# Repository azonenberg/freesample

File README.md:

# freesample
High performance sampling oscilloscope based on INTEGRALSTICK

Separate board talking to AC701 since we need a GTP
	Use a XM105 if we need more GPIO and

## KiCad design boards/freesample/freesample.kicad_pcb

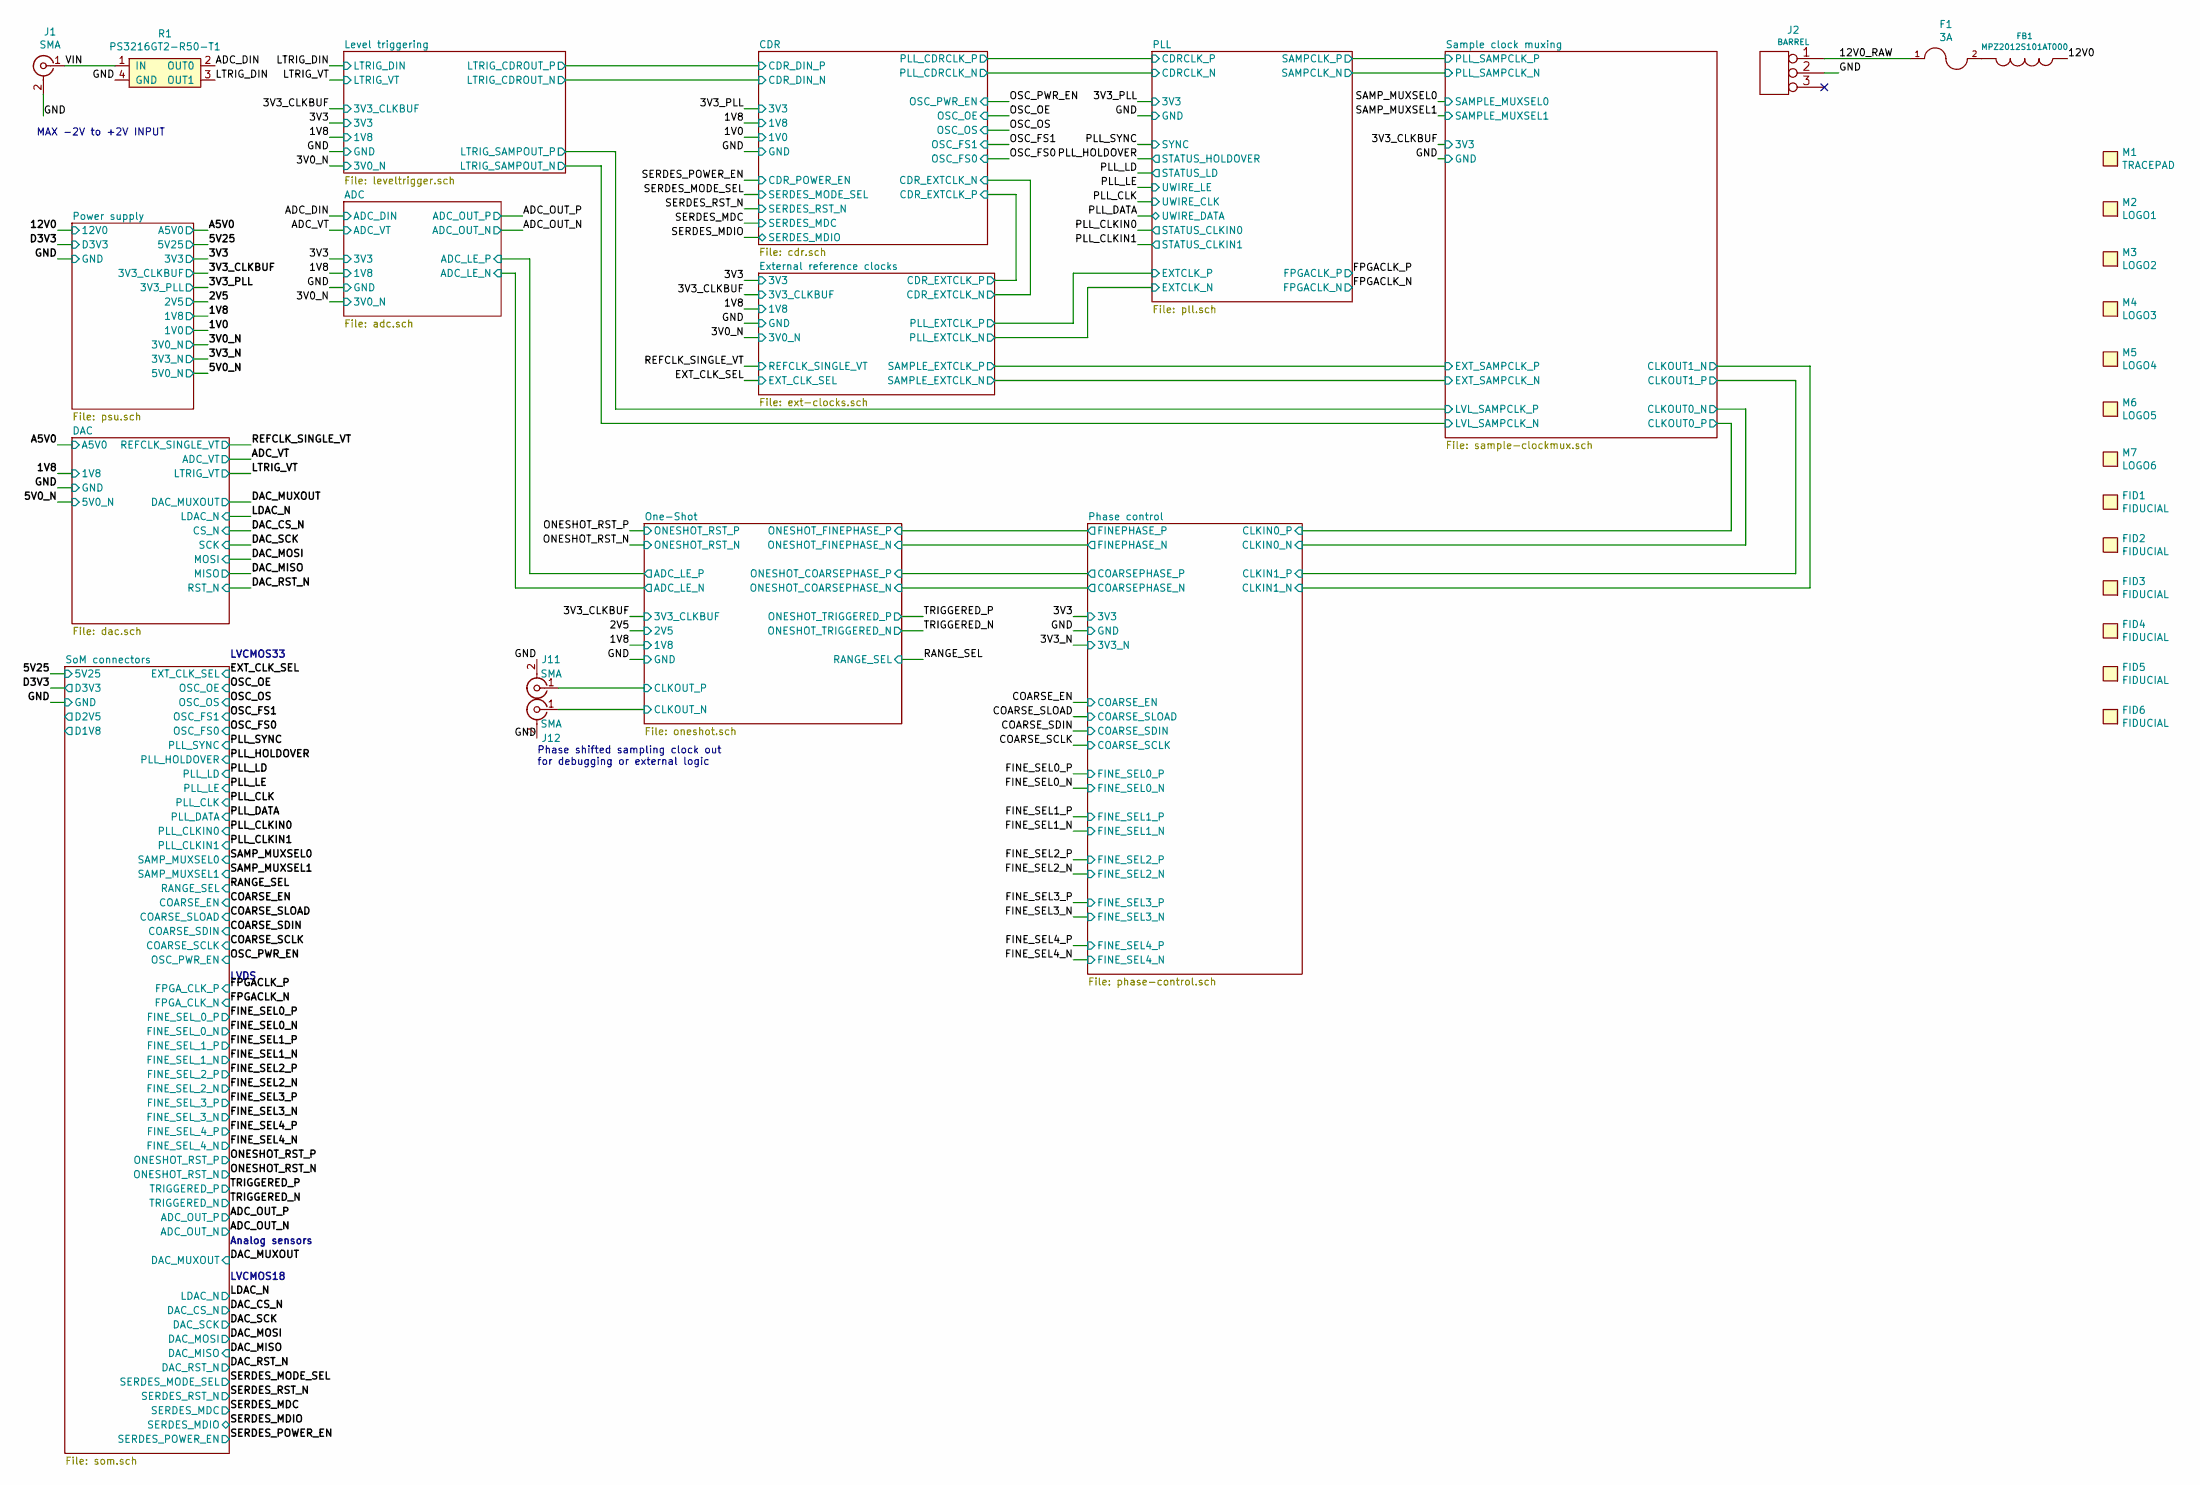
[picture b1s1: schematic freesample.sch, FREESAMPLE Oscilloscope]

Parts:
F1: 3A; EIA_0603_RES_NOSILK
FB1: MPZ2012S101AT000; EIA_0805_CAP_NOSILK
FID1, FID2, FID3, FID4, FID5, FID6: FIDUCIAL; FIDUCIAL_1MM
J1, J11, J12: SMA; CONN_SMA_EDGE_SAMTEC_SMA_J_P_H_ST_EM1
J2: BARREL; CONN_CUI_PJ-058BH_HIPWR_BARREL_NOSLOT
M1: TRACEPAD; SERIALNUM_MOLEX_0916580020
M2: LOGO1; LONGTHING-1200DPI
M3: LOGO2; Logo_silk_OSHW_6x6mm
M4: LOGO3; Logo_silk_polarity_center_5x1.4mm
M5: LOGO4; Logo_silk_ROHS_5x2.8mm
M6: LOGO5; Logo_silk_warning_5x4.2mm
M7: LOGO6; Logo_silk_WEEE_3.4x5mm
R1: PS3216GT2-R50-T1‎; SPLITTER_SUSUMU_PS3216G

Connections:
/12V0: FB1.1; also elsewhere on the board
/12V0_RAW: F1.1, J2.1
/ADC_DIN: R1.2 (OUT0); also elsewhere on the board
/GND: J1.2 (Ext), J2.2 (PM), J11.2 (Ext), J12.2 (Ext), R1.4 (GND); also elsewhere on the board
/LTRIG_DIN: R1.3 (OUT1); also elsewhere on the board
/One-Shot/CLKOUT_N: J12.1 (In); also elsewhere on the board
/One-Shot/CLKOUT_P: J11.1 (In); also elsewhere on the board
/VIN: J1.1 (In), R1.1 (IN)
unnamed: F1.2, FB1.2

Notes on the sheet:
LVCMOS33
Analog sensors
LVCMOS18
MAX -2V to +2V INPUT
LVDS
Phase shifted sampling clock out for debugging or external logic

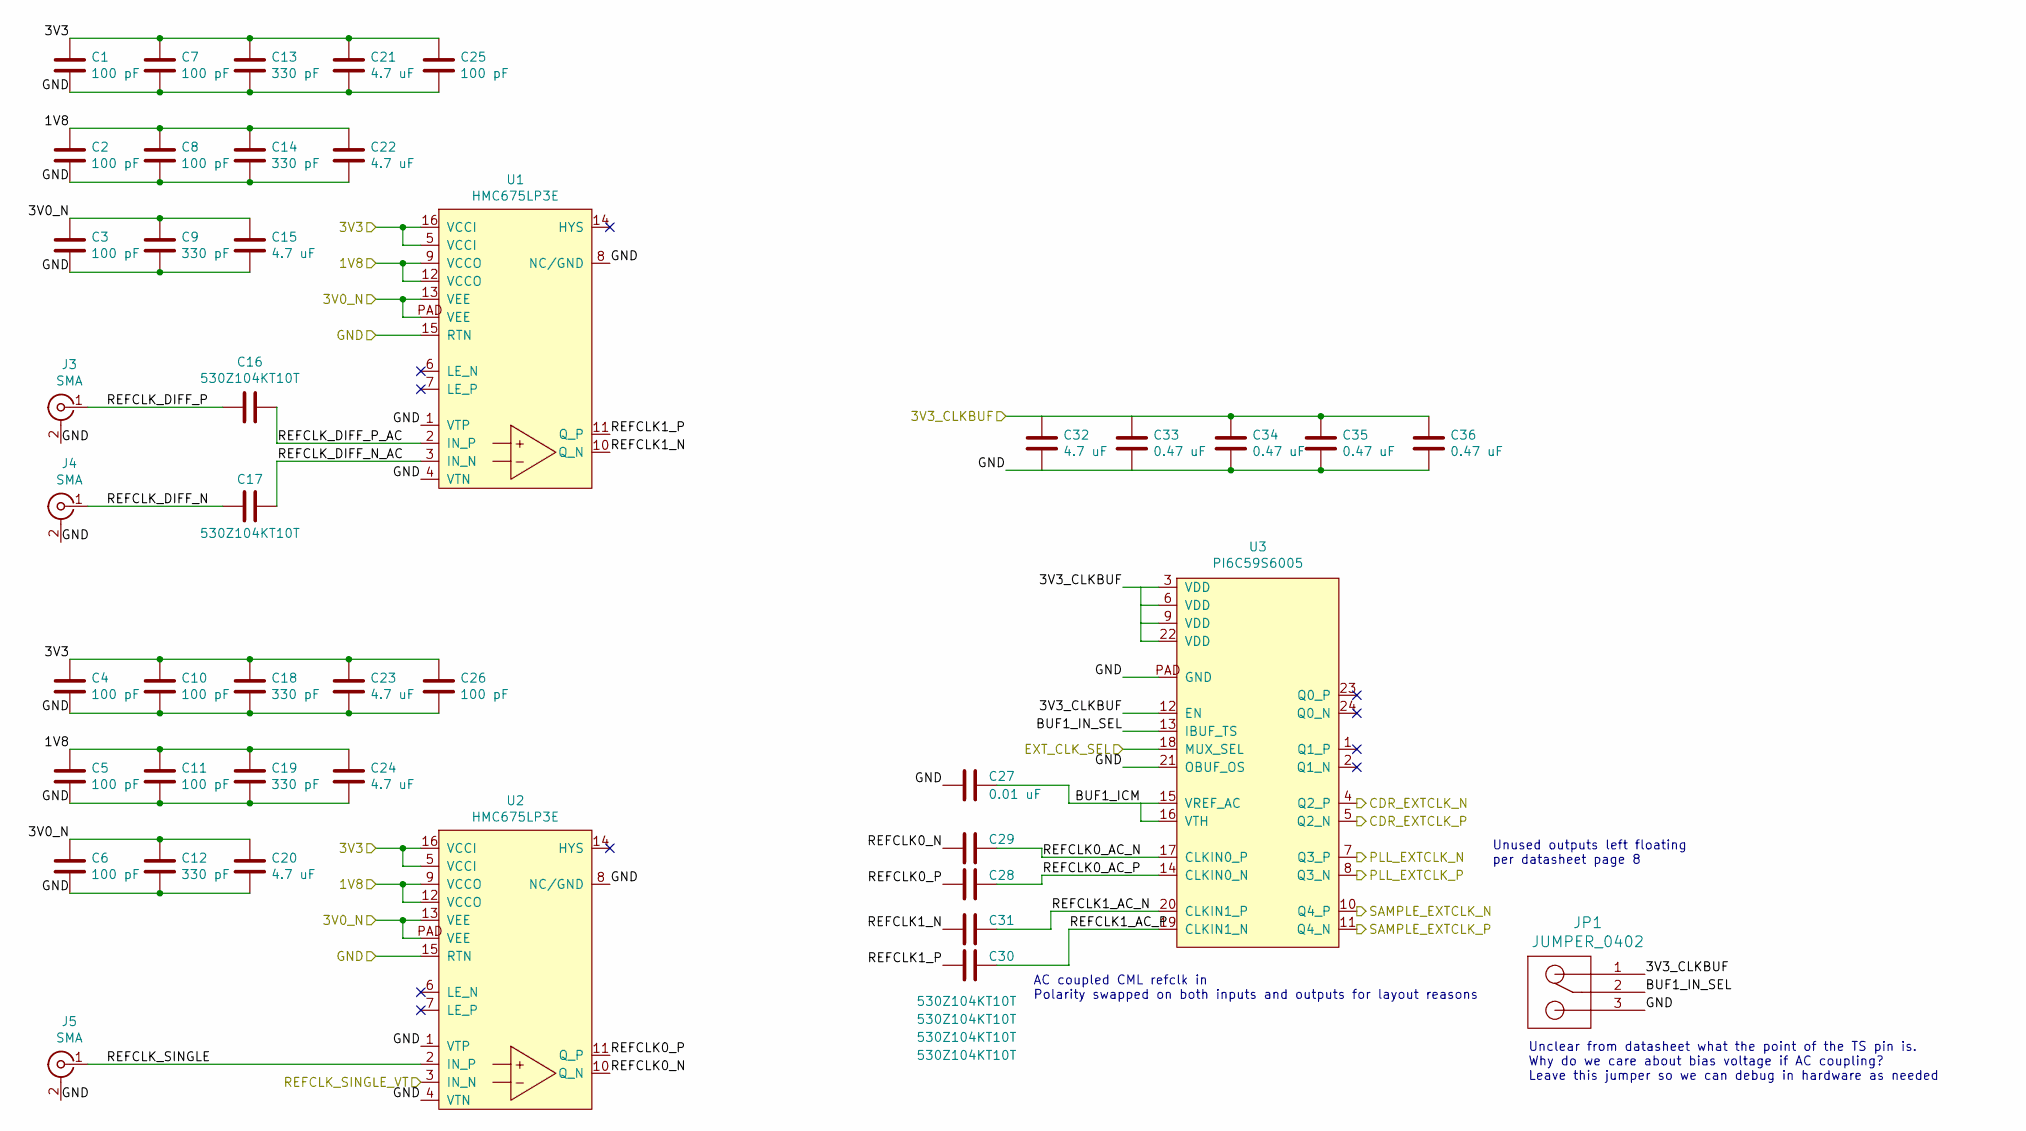
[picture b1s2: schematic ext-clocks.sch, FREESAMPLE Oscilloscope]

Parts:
C1, C2, C3, C4, C5, C6, C7, C8, C10, C11, C25, C26: 100 pF; EIA_0201_CAP_NOSILK
C9, C12, C13, C14, C18, C19: 330 pF; EIA_0201_CAP_NOSILK
C15, C20, C21, C22, C23, C24, C32: 4.7 uF; EIA_0603_CAP_NOSILK
C16, C17, C28, C29, C30, C31: 530Z104KT10T; EIA_0201_CAP_NOSILK
C27: 0.01 uF; EIA_0402_CAP_NOSILK
C33, C34, C35, C36: 0.47 uF; EIA_0402_CAP_NOSILK
J3, J4, J5: SMA; CONN_SMA_EDGE_SAMTEC_SMA_J_P_H_ST_EM1
JP1: JUMPER_0402; EIA_0402_JUMPER
U1, U2: HMC675LP3E; QFN_16_0.5MM_3x3MM
U3: PI6C59S6005; QFN_24_0.5MM_4x4MM

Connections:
/1V8: C2.1, C5.1, C8.1, C11.1, C14.1, C19.1, C22.1, C24.1, U1.9 (VCCO), U1.12 (VCCO), U2.9 (VCCO), U2.12 (VCCO); also elsewhere on the board
/3V0_N: C3.1, C6.1, C9.1, C12.1, C15.1, C20.1, U1.13 (VEE), U1.PAD (VEE), U2.13 (VEE), U2.PAD (VEE); also elsewhere on the board
/3V3: C1.1, C4.1, C7.1, C10.1, C13.1, C18.1, C21.1, C23.1, C25.1, C26.1, U1.5 (VCCI), U1.16 (VCCI), U2.5 (VCCI), U2.16 (VCCI); also elsewhere on the board
/3V3_CLKBUF: C32.1, C33.1, C34.1, C35.1, C36.1, JP1.1, U3.3 (VDD), U3.6 (VDD), U3.9 (VDD), U3.12 (EN), U3.22 (VDD); also elsewhere on the board
/CDR/CDR_EXTCLK_N: U3.4 (Q2_P); also elsewhere on the board
/CDR/CDR_EXTCLK_P: U3.5 (Q2_N); also elsewhere on the board
/EXT_CLK_SEL: U3.18 (MUX_SEL); also elsewhere on the board
/External reference clocks/BUF1_ICM: C27.1, U3.15 (VREF_AC), U3.16 (VTH)
/External reference clocks/BUF1_IN_SEL: JP1.2, U3.13 (IBUF_TS)
/External reference clocks/REFCLK0_AC_N: C29.1, U3.17 (CLKIN0_P)
/External reference clocks/REFCLK0_AC_P: C28.1, U3.14 (CLKIN0_N)
/External reference clocks/REFCLK0_N: C29.2, U2.10 (Q_N)
/External reference clocks/REFCLK0_P: C28.2, U2.11 (Q_P)
/External reference clocks/REFCLK1_AC_N: C31.1, U3.20 (CLKIN1_P)
/External reference clocks/REFCLK1_AC_P: C30.1, U3.19 (CLKIN1_N)
/External reference clocks/REFCLK1_N: C31.2, U1.10 (Q_N)
/External reference clocks/REFCLK1_P: C30.2, U1.11 (Q_P)
/External reference clocks/REFCLK_DIFF_N: C17.2, J4.1 (In)
/External reference clocks/REFCLK_DIFF_N_AC: C17.1, U1.3 (IN_N)
/External reference clocks/REFCLK_DIFF_P: C16.2, J3.1 (In)
/External reference clocks/REFCLK_DIFF_P_AC: C16.1, U1.2 (IN_P)
/External reference clocks/REFCLK_SINGLE: J5.1 (In), U2.2 (IN_P)
/GND: C1.2, C2.2, C3.2, C4.2, C5.2, C6.2, C7.2, C8.2, C9.2, C10.2, C11.2, C12.2, C13.2, C14.2, C15.2, C18.2, C19.2, C20.2, C21.2, C22.2, C23.2, C24.2, C25.2, C26.2, C27.2, C32.2, C33.2, C34.2, C35.2, C36.2, J3.2 (Ext), J4.2 (Ext), J5.2 (Ext), JP1.3, U1.1 (VTP), U1.4 (VTN), U1.8 (NC/GND), U1.15 (RTN), U2.1 (VTP), U2.4 (VTN), U2.8 (NC/GND), U2.15 (RTN), U3.21 (OBUF_OS), U3.PAD (GND); also elsewhere on the board
/PLL/EXTCLK_N: U3.7 (Q3_P); also elsewhere on the board
/PLL/EXTCLK_P: U3.8 (Q3_N); also elsewhere on the board
/REFCLK_SINGLE_VT: U2.3 (IN_N); also elsewhere on the board
/Sample clock muxing/EXT_SAMPCLK_N: U3.10 (Q4_P); also elsewhere on the board
/Sample clock muxing/EXT_SAMPCLK_P: U3.11 (Q4_N); also elsewhere on the board

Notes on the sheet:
AC coupled CML refclk in Polarity swapped on both inputs and outputs for layout reasons
Unused outputs left floating per datasheet page 8
Unclear from datasheet what the point of the TS pin is. Why do we care about bias voltage if AC coupling? Leave this jumper so we can debug in hardware as needed

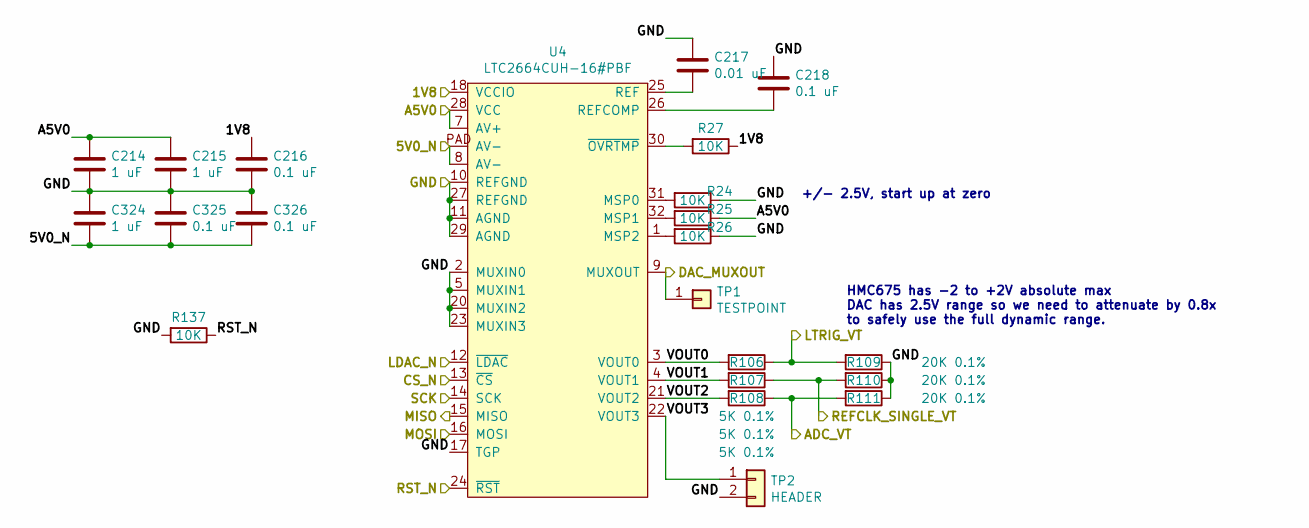
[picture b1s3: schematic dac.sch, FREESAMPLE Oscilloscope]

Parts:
C214, C215, C324: 1 uF; EIA_0603_CAP_NOSILK
C216, C218, C325, C326: 0.1 uF; EIA_0402_CAP_NOSILK
C217: 0.01 uF; EIA_0402_CAP_NOSILK
R24, R25, R26, R27, R137: 10K; EIA_0402_RES_NOSILK
R106, R107, R108: 5K 0.1%; EIA_0402_RES_NOSILK
R109, R110, R111: 20K 0.1%; EIA_0402_RES_NOSILK
TP1: TESTPOINT; TESTPOINT_SMT_KEYSTONE_5016
TP2: HEADER; CONN_HEADER_2.54MM_1x2
U4: LTC2664CUH-16#PBF; QFN_32_0.5MM_5x5MM

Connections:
/1V8: C216.1, R27.1, U4.18 (VCCIO); also elsewhere on the board
/5V0_N: C324.2, C325.2, C326.2, U4.8 (AV-), U4.PAD (AV-); also elsewhere on the board
/A5V0: C214.1, C215.1, R25.1, U4.7 (AV+), U4.28 (VCC); also elsewhere on the board
/ADC_VT: R108.1, R111.2; also elsewhere on the board
/DAC/VOUT0: R106.2, U4.3 (VOUT0)
/DAC/VOUT1: R107.2, U4.4 (VOUT1)
/DAC/VOUT2: R108.2, U4.21 (VOUT2)
/DAC/VOUT3: TP2.1, U4.22 (VOUT3)
/DAC_CS_N: U4.13 (~CS); also elsewhere on the board
/DAC_MISO: U4.15 (MISO); also elsewhere on the board
/DAC_MOSI: U4.16 (MOSI); also elsewhere on the board
/DAC_MUXOUT: TP1.1, U4.9 (MUXOUT); also elsewhere on the board
/DAC_RST_N: R137.1, U4.24 (~RST); also elsewhere on the board
/DAC_SCK: U4.14 (SCK); also elsewhere on the board
/GND: C214.2, C215.2, C216.2, C217.1, C218.1, C324.1, C325.1, C326.1, R24.1, R26.1, R109.1, R110.1, R111.1, R137.2, TP2.2, U4.2 (MUXIN0), U4.5 (MUXIN1), U4.10 (REFGND), U4.11 (AGND), U4.17 (TGP), U4.20 (MUXIN2), U4.23 (MUXIN3), U4.27 (REFGND), U4.29 (AGND); also elsewhere on the board
/LDAC_N: U4.12 (~LDAC); also elsewhere on the board
/LTRIG_VT: R106.1, R109.2; also elsewhere on the board
/REFCLK_SINGLE_VT: R107.1, R110.2; also elsewhere on the board
unnamed: C217.2, U4.25 (REF)
unnamed: C218.2, U4.26 (REFCOMP)
unnamed: R24.2, U4.31 (MSP0)
unnamed: R25.2, U4.32 (MSP1)
unnamed: R26.2, U4.1 (MSP2)
unnamed: R27.2, U4.30 (~OVRTMP)

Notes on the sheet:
+/- 2.5V, start up at zero
HMC675 has -2 to +2V absolute max DAC has 2.5V range so we need to attenuate by 0.8x to safely use the full dynamic range.

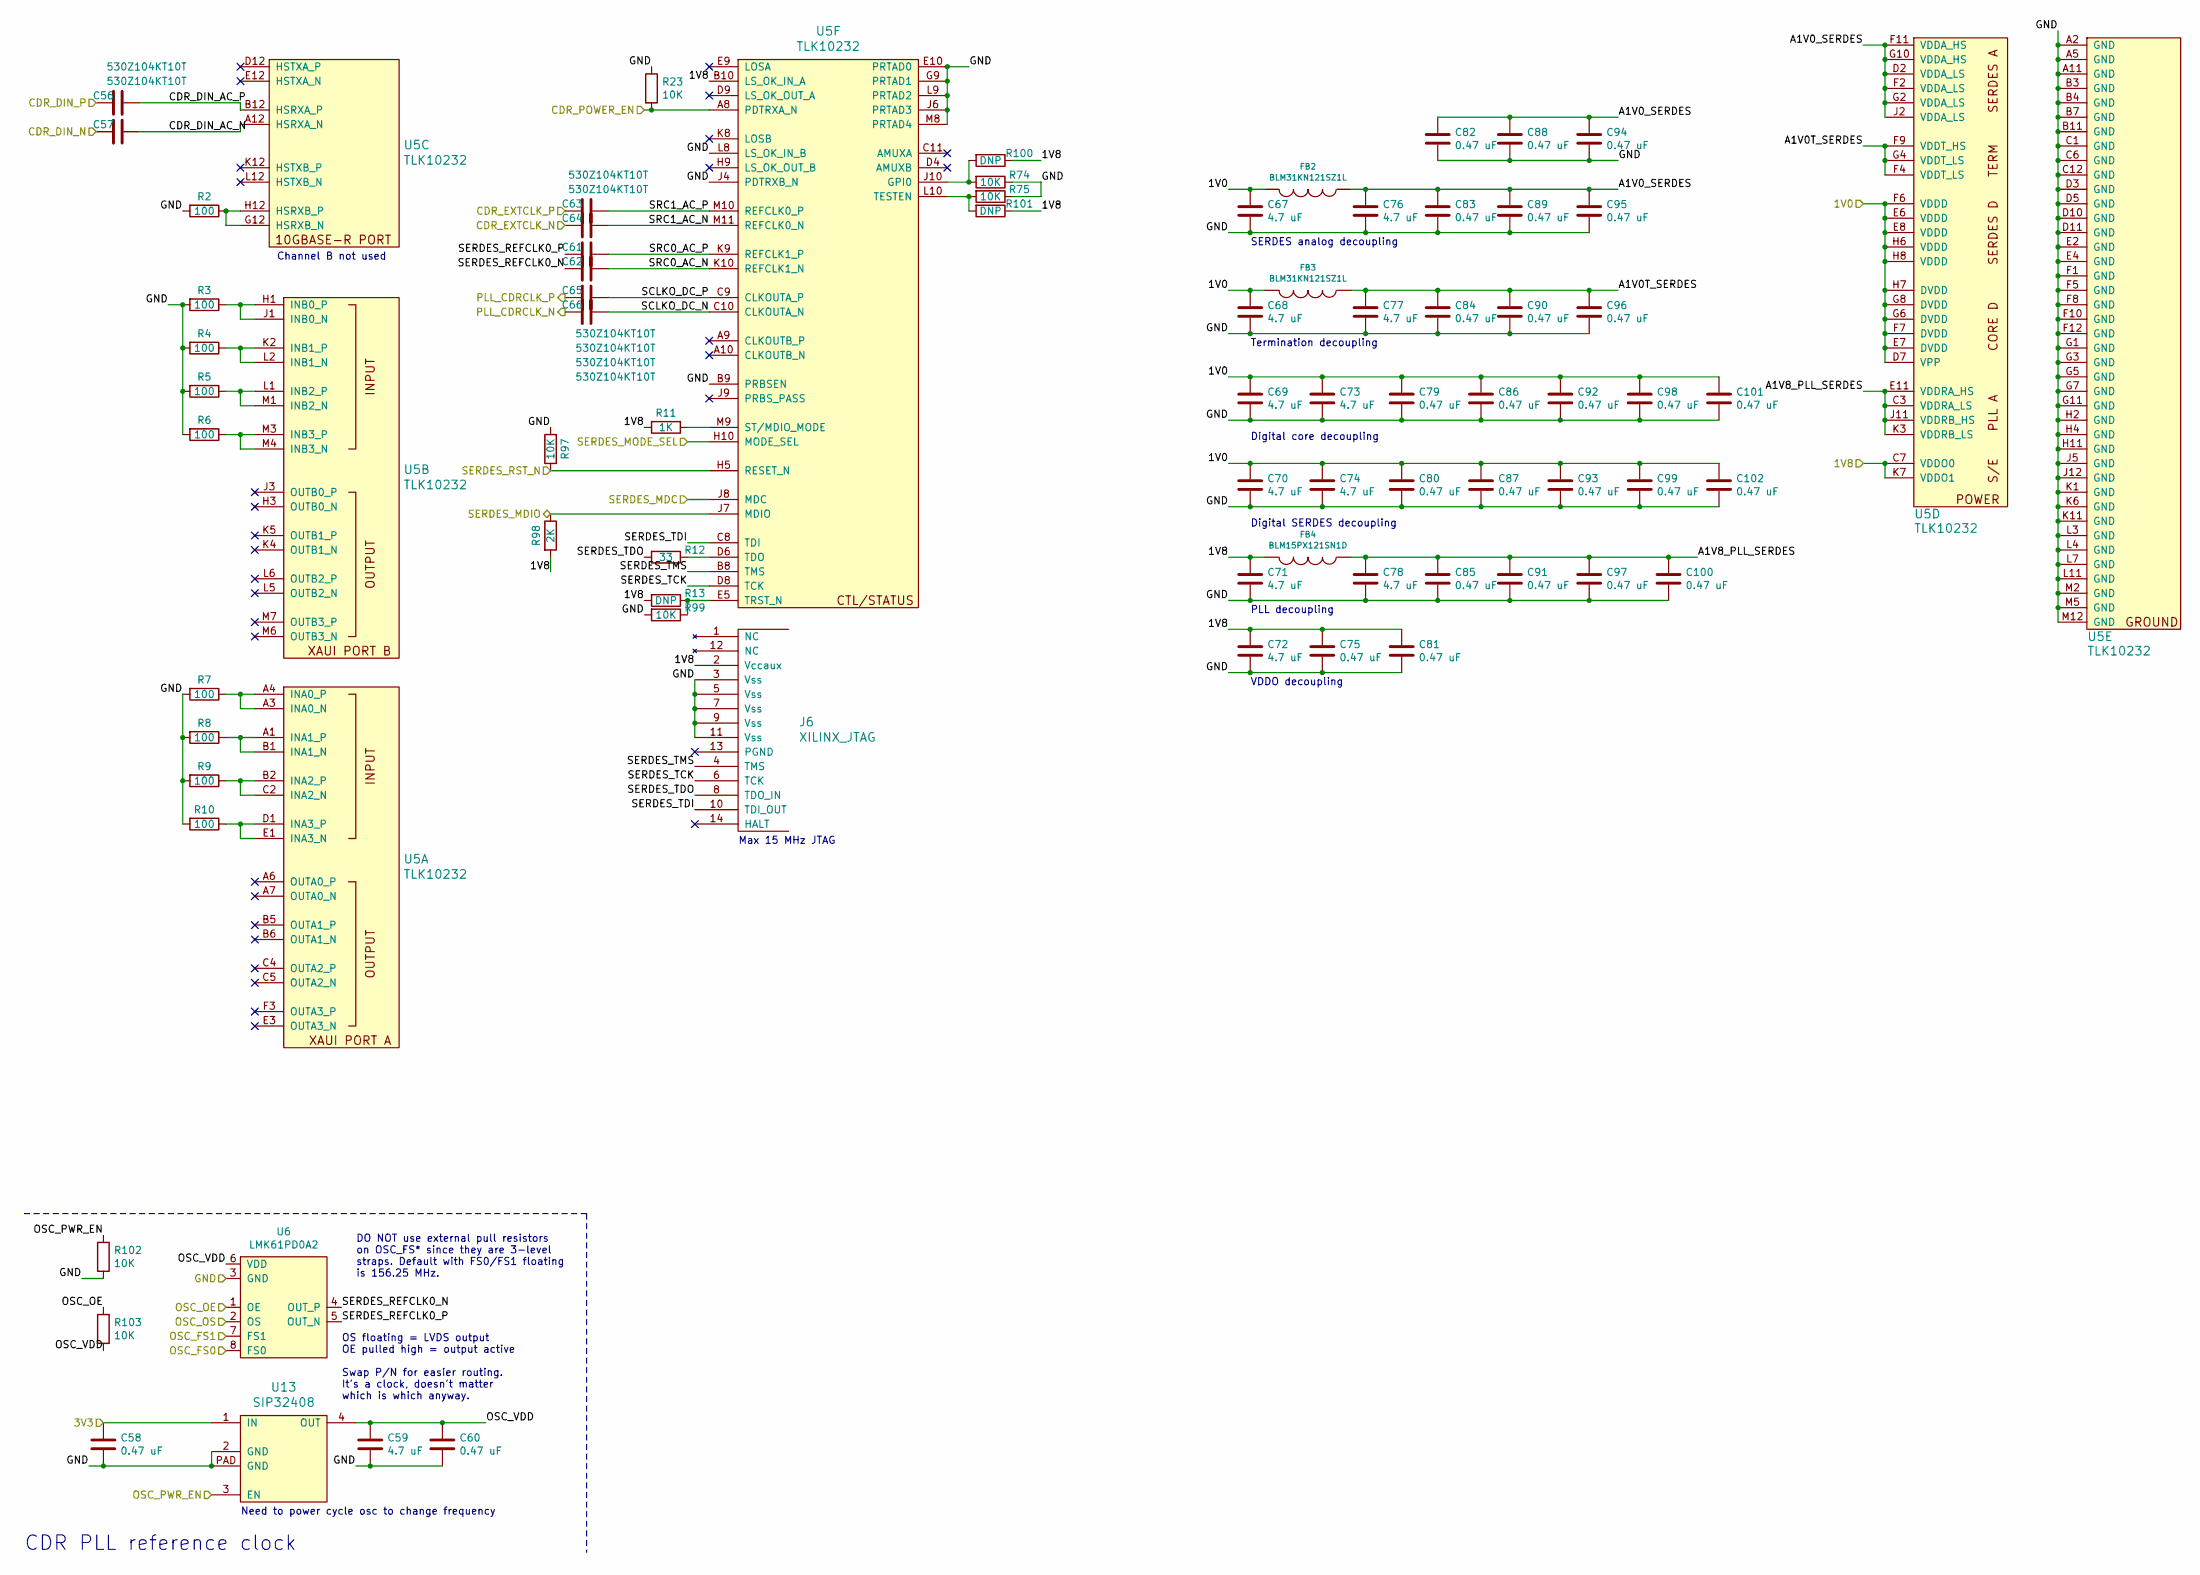
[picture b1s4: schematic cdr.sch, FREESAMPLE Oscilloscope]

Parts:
C56, C57, C61, C62, C63, C64, C65, C66: 530Z104KT10T; EIA_0201_CAP_NOSILK
C58, C60, C75, C79, C80, C81, C82, C83, C84, C85, C86, C87, C88, C89, C90, C91, C92, C93, C94, C95, C96, C97, C98, C99, C100, C101, C102: 0.47 uF; EIA_0402_CAP_NOSILK
C59, C67, C68, C69, C70, C71, C72, C73, C74, C76, C77, C78: 4.7 uF; EIA_0603_CAP_NOSILK
FB2, FB3: BLM31KN121SZ1L; EIA_1206_CAP_NOSILK
FB4: BLM15PX121SN1D; EIA_0402_CAP_NOSILK
J6: XILINX_JTAG; XILINX_JTAG_PTH_MOLEX_0878311420
R2, R3, R4, R5, R6, R7, R8, R9, R10: 100; EIA_0402_RES_NOSILK
R11: 1K; EIA_0402_RES_NOSILK
R12: 33; EIA_0402_RES_NOSILK
R13, R100, R101: DNP; EIA_0402_RES_NOSILK
R23, R74, R75, R97, R99, R102, R103: 10K; EIA_0402_RES_NOSILK
R98: 2K; EIA_0402_RES_NOSILK
U5: TLK10232; BGA_144_13x13_FULLARRAY_1MM
U6: LMK61PD0A2; QFN_8_5x7MM_TI_SIA
U13: SIP32408; DFN_4_0.5MM_1.6x1.2MM

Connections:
/1V0: C67.1, C68.1, C69.1, C70.1, C73.1, C74.1, C79.1, C80.1, C86.1, C87.1, C92.1, C93.1, C98.1, C99.1, C101.1, C102.1, FB2.2, FB3.2, U5.D7 (VPP), U5.E6 (VDDD), U5.E7 (DVDD), U5.E8 (VDDD), U5.F6 (VDDD), U5.F7 (DVDD), U5.G6 (DVDD), U5.G8 (DVDD), U5.H6 (VDDD), U5.H7 (DVDD), U5.H8 (VDDD); also elsewhere on the board
/1V8: C71.1, C72.1, C75.1, C81.1, FB4.2, J6.2 (Vccaux), R11.2, R13.2, R98.2, R100.1, R101.1, U5.B10 (LS_OK_IN_A), U5.C7 (VDDO0), U5.K7 (VDDO1); also elsewhere on the board
/3V3_PLL: C58.1, U13.1 (IN); also elsewhere on the board
/CDR/A1V0T_SERDES: C77.1, C84.1, C90.1, C96.1, FB3.1, U5.F4 (VDDT_LS), U5.F9 (VDDT_HS), U5.G4 (VDDT_LS)
/CDR/A1V0_SERDES: C76.1, C82.1, C83.1, C88.1, C89.1, C94.1, C95.1, FB2.1, U5.D2 (VDDA_LS), U5.F2 (VDDA_LS), U5.F11 (VDDA_HS), U5.G2 (VDDA_LS), U5.G10 (VDDA_HS), U5.J2 (VDDA_LS)
/CDR/A1V8_PLL_SERDES: C78.1, C85.1, C91.1, C97.1, C100.1, FB4.1, U5.C3 (VDDRA_LS), U5.E11 (VDDRA_HS), U5.J11 (VDDRB_HS), U5.K3 (VDDRB_LS)
/CDR/CDR_DIN_AC_N: C57.1, U5.A12 (HSRXA_N)
/CDR/CDR_DIN_AC_P: C56.1, U5.B12 (HSRXA_P)
/CDR/CDR_DIN_N: C57.2; also elsewhere on the board
/CDR/CDR_DIN_P: C56.2; also elsewhere on the board
/CDR/CDR_EXTCLK_N: C64.2; also elsewhere on the board
/CDR/CDR_EXTCLK_P: C63.2; also elsewhere on the board
/CDR/OSC_VDD: C59.1, C60.1, R103.2, U6.6 (VDD), U13.4 (OUT)
/CDR/SCLKO_DC_N: C66.1, U5.C10 (CLKOUTA_N)
/CDR/SCLKO_DC_P: C65.1, U5.C9 (CLKOUTA_P)
/CDR/SERDES_REFCLK0_N: C62.2, U6.4 (OUT_P)
/CDR/SERDES_REFCLK0_P: C61.2, U6.5 (OUT_N)
/CDR/SERDES_TCK: J6.6 (TCK), U5.D8 (TCK)
/CDR/SERDES_TDI: J6.10 (TDI_OUT), U5.C8 (TDI)
/CDR/SERDES_TDO: J6.8 (TDO_IN), R12.2
/CDR/SERDES_TMS: J6.4 (TMS), U5.B8 (TMS)
/CDR/SRC0_AC_N: C62.1, U5.K10 (REFCLK1_N)
/CDR/SRC0_AC_P: C61.1, U5.K9 (REFCLK1_P)
/CDR/SRC1_AC_N: C64.1, U5.M11 (REFCLK0_N)
/CDR/SRC1_AC_P: C63.1, U5.M10 (REFCLK0_P)
/GND: C58.2, C59.2, C60.2, C67.2, C68.2, C69.2, C70.2, C71.2, C72.2, C73.2, C74.2, C75.2, C76.2, C77.2, C78.2, C79.2, C80.2, C81.2, C82.2, C83.2, C84.2, C85.2, C86.2, C87.2, C88.2, C89.2, C90.2, C91.2, C92.2, C93.2, C94.2, C95.2, C96.2, C97.2, C98.2, C99.2, C100.2, C101.2, C102.2, J6.3 (Vss), J6.5 (Vss), J6.7 (Vss), J6.9 (Vss), J6.11 (Vss), R2.2, R3.2, R4.2, R5.2, R6.2, R7.2, R8.2, R9.2, R10.2, R23.1, R74.1, R75.1, R97.2, R99.2, R102.2, U5.A2 (GND), U5.A5 (GND), U5.A11 (GND), U5.B3 (GND), U5.B4 (GND), U5.B7 (GND), U5.B9 (PRBSEN), U5.B11 (GND), U5.C1 (GND), U5.C6 (GND), U5.C12 (GND), U5.D3 (GND), U5.D5 (GND), U5.D10 (GND), U5.D11 (GND), U5.E2 (GND), U5.E4 (GND), U5.E10 (PRTAD0), U5.F1 (GND), U5.F5 (GND), U5.F8 (GND), U5.F10 (GND), U5.F12 (GND), U5.G1 (GND), U5.G3 (GND), U5.G5 (GND), U5.G7 (GND), U5.G9 (PRTAD1), U5.G11 (GND), U5.H2 (GND), U5.H4 (GND), U5.H11 (GND), U5.J4 (PDTRXB_N), U5.J5 (GND), U5.J6 (PRTAD3), U5.J12 (GND), U5.K1 (GND), U5.K6 (GND), U5.K11 (GND), U5.L3 (GND), U5.L4 (GND), U5.L7 (GND), U5.L8 (LS_OK_IN_B), U5.L9 (PRTAD2), U5.L11 (GND), U5.M2 (GND), U5.M5 (GND), U5.M8 (PRTAD4), U5.M12 (GND), U6.3 (GND), U13.2 (GND), U13.PAD (GND); also elsewhere on the board
/OSC_FS0: U6.8 (FS0); also elsewhere on the board
/OSC_FS1: U6.7 (FS1); also elsewhere on the board
/OSC_OE: R103.1, U6.1 (OE); also elsewhere on the board
/OSC_OS: U6.2 (OS); also elsewhere on the board
/OSC_PWR_EN: R102.1, U13.3 (EN); also elsewhere on the board
/PLL/CDRCLK_N: C66.2; also elsewhere on the board
/PLL/CDRCLK_P: C65.2; also elsewhere on the board
/SERDES_MDC: U5.J8 (MDC); also elsewhere on the board
/SERDES_MDIO: R98.1, U5.J7 (MDIO); also elsewhere on the board
/SERDES_MODE_SEL: U5.H10 (MODE_SEL); also elsewhere on the board
/SERDES_POWER_EN: R23.2, U5.A8 (PDTRXA_N); also elsewhere on the board
/SERDES_RST_N: R97.1, U5.H5 (RESET_N); also elsewhere on the board
unnamed: R2.1, U5.G12 (HSRXB_N), U5.H12 (HSRXB_P)
unnamed: R3.1, U5.H1 (INB0_P), U5.J1 (INB0_N)
unnamed: R4.1, U5.K2 (INB1_P), U5.L2 (INB1_N)
unnamed: R5.1, U5.L1 (INB2_P), U5.M1 (INB2_N)
unnamed: R6.1, U5.M3 (INB3_P), U5.M4 (INB3_N)
unnamed: R7.1, U5.A3 (INA0_N), U5.A4 (INA0_P)
unnamed: R8.1, U5.A1 (INA1_P), U5.B1 (INA1_N)
unnamed: R9.1, U5.B2 (INA2_P), U5.C2 (INA2_N)
unnamed: R10.1, U5.D1 (INA3_P), U5.E1 (INA3_N)
unnamed: R11.1, U5.M9 (ST/MDIO_MODE)
unnamed: R12.1, U5.D6 (TDO)
unnamed: R13.1, R99.1, U5.E5 (TRST_N)
unnamed: R74.2, R100.2, U5.J10 (GPI0)
unnamed: R75.2, R101.2, U5.L10 (TESTEN)

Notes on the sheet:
Channel B not used
Need to power cycle osc to change frequency
Max 15 MHz JTAG
VDDO decoupling
PLL decoupling
Digital SERDES decoupling
Digital core decoupling
Termination decoupling
SERDES analog decoupling
CDR PLL reference clock
DO NOT use external pull resistors on OSC_FS* since they are 3-level straps. Default with FS0/FS1 floating is 156.25 MHz.
OS floating = LVDS output OE pulled high = output active Swap P/N for easier routing. It's a clock, doesn't matter which is which anyway.

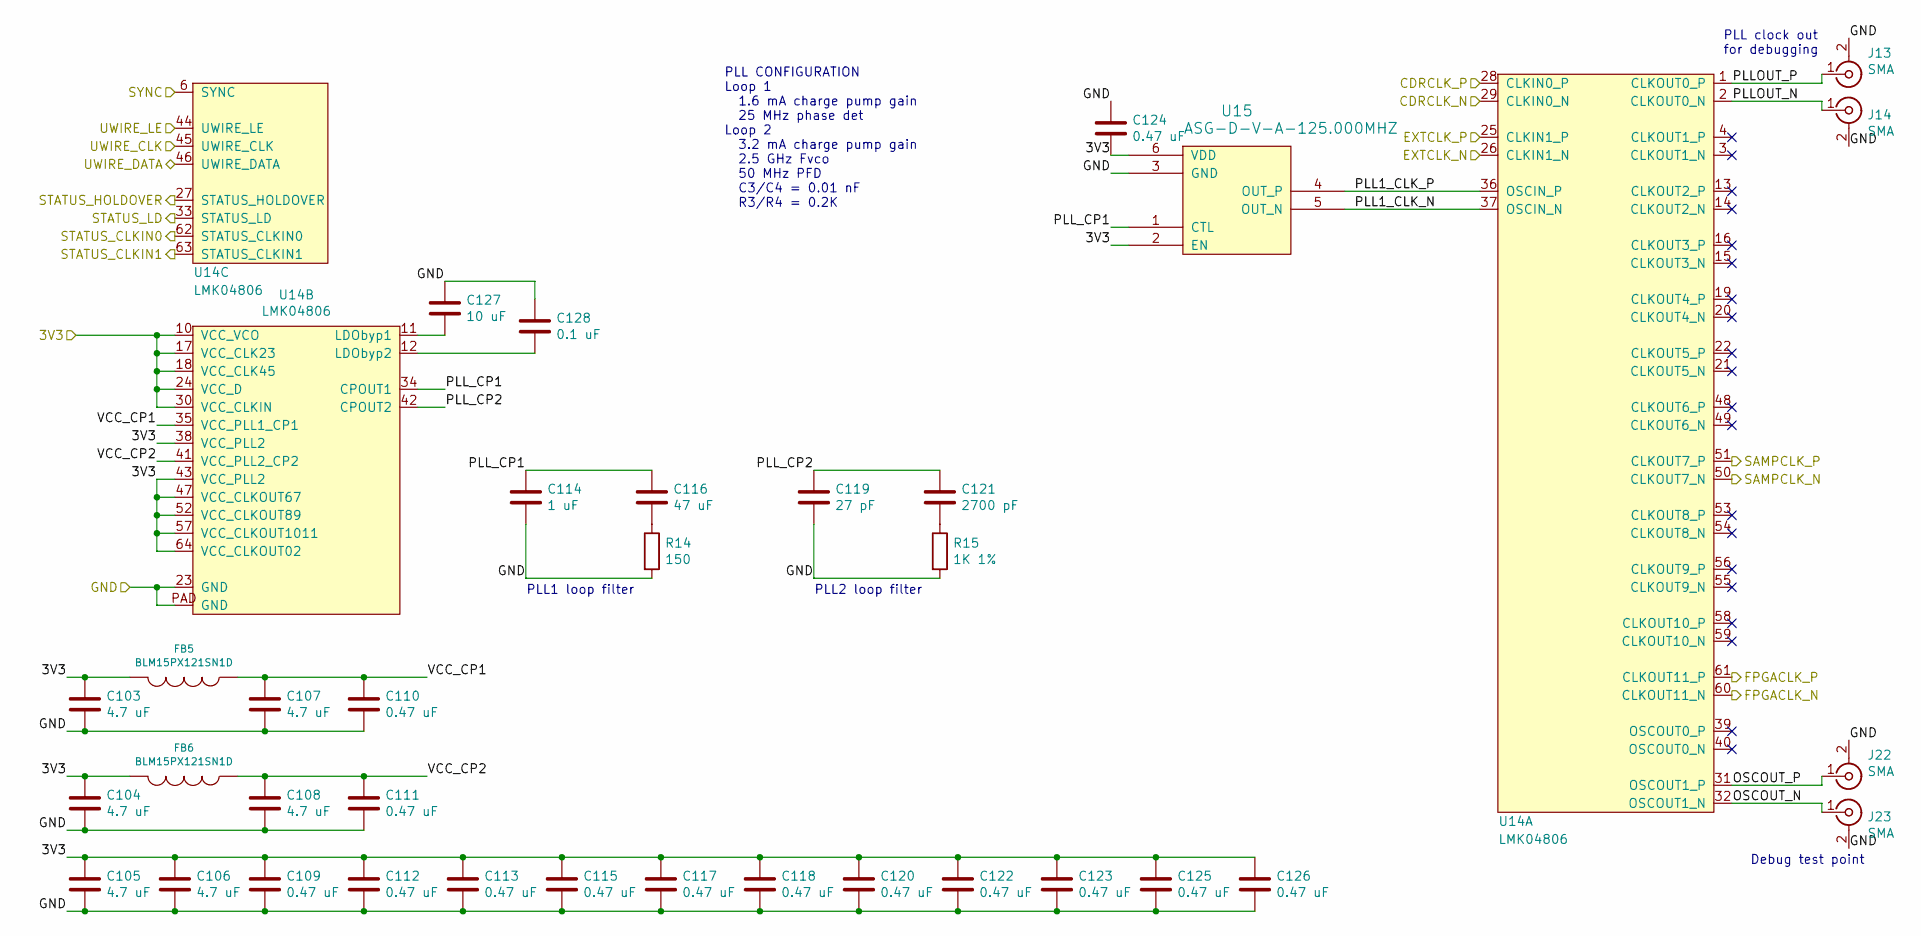
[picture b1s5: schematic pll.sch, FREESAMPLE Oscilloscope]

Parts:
C103, C104, C105, C106, C107, C108: 4.7 uF; EIA_0603_CAP_NOSILK
C109, C110, C111, C112, C113, C115, C117, C118, C120, C122, C123, C124, C125, C126: 0.47 uF; EIA_0402_CAP_NOSILK
C114: 1 uF; EIA_0402_CAP_NOSILK
C116: 47 uF; EIA_1210_CAP_NOSILK
C119: 27 pF; EIA_0402_CAP_NOSILK
C121: 2700 pF; EIA_0402_CAP_NOSILK
C127: 10 uF; EIA_1206_CAP_NOSILK
C128: 0.1 uF; EIA_0402_CAP_NOSILK
FB5, FB6: BLM15PX121SN1D; EIA_0402_CAP_NOSILK
J13, J14, J22, J23: SMA; CONN_SMA_EDGE_SAMTEC_SMA_J_P_H_ST_EM1
R14: 150; EIA_0402_RES_NOSILK
R15: 1K 1%; EIA_0402_RES_NOSILK
U14: LMK04806; QFN_64_0.5MM_9x9MM
U15: ASG-D-V-A-125.000MHZ; VCXO_5x7MM_ASG_D

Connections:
/3V3_PLL: C103.1, C104.1, C105.1, C106.1, C109.1, C112.1, C113.1, C115.1, C117.1, C118.1, C120.1, C122.1, C123.1, C124.2, C125.1, C126.1, FB5.2, FB6.2, U14.10 (VCC_VCO), U14.17 (VCC_CLK23), U14.18 (VCC_CLK45), U14.24 (VCC_D), U14.30 (VCC_CLKIN), U14.38 (VCC_PLL2), U14.43 (VCC_PLL2), U14.47 (VCC_CLKOUT67), U14.52 (VCC_CLKOUT89), U14.57 (VCC_CLKOUT1011), U14.64 (VCC_CLKOUT02), U15.2 (EN), U15.6 (VDD); also elsewhere on the board
/FPGACLK_N: U14.60 (CLKOUT11_N); also elsewhere on the board
/FPGACLK_P: U14.61 (CLKOUT11_P); also elsewhere on the board
/GND: C103.2, C104.2, C105.2, C106.2, C107.2, C108.2, C109.2, C110.2, C111.2, C112.2, C113.2, C114.2, C115.2, C117.2, C118.2, C119.2, C120.2, C122.2, C123.2, C124.1, C125.2, C126.2, C127.1, C128.1, J13.2 (Ext), J14.2 (Ext), J22.2 (Ext), J23.2 (Ext), R14.2, R15.2, U14.23 (GND), U14.PAD (GND), U15.3 (GND); also elsewhere on the board
/PLL/CDRCLK_N: U14.29 (CLKIN0_N); also elsewhere on the board
/PLL/CDRCLK_P: U14.28 (CLKIN0_P); also elsewhere on the board
/PLL/EXTCLK_N: U14.26 (CLKIN1_N); also elsewhere on the board
/PLL/EXTCLK_P: U14.25 (CLKIN1_P); also elsewhere on the board
/PLL/OSCOUT_N: J23.1 (In), U14.32 (OSCOUT1_N)
/PLL/OSCOUT_P: J22.1 (In), U14.31 (OSCOUT1_P)
/PLL/PLL1_CLK_N: U14.37 (OSCIN_N), U15.5 (OUT_N)
/PLL/PLL1_CLK_P: U14.36 (OSCIN_P), U15.4 (OUT_P)
/PLL/PLLOUT_N: J14.1 (In), U14.2 (CLKOUT0_N)
/PLL/PLLOUT_P: J13.1 (In), U14.1 (CLKOUT0_P)
/PLL/PLL_CP1: C114.1, C116.1, U14.34 (CPOUT1), U15.1 (CTL)
/PLL/PLL_CP2: C119.1, C121.1, U14.42 (CPOUT2)
/PLL/VCC_CP1: C107.1, C110.1, FB5.1, U14.35 (VCC_PLL1_CP1)
/PLL/VCC_CP2: C108.1, C111.1, FB6.1, U14.41 (VCC_PLL2_CP2)
/PLL_CLK: U14.45 (UWIRE_CLK); also elsewhere on the board
/PLL_CLKIN0: U14.62 (STATUS_CLKIN0); also elsewhere on the board
/PLL_CLKIN1: U14.63 (STATUS_CLKIN1); also elsewhere on the board
/PLL_DATA: U14.46 (UWIRE_DATA); also elsewhere on the board
/PLL_HOLDOVER: U14.27 (STATUS_HOLDOVER); also elsewhere on the board
/PLL_LD: U14.33 (STATUS_LD); also elsewhere on the board
/PLL_LE: U14.44 (UWIRE_LE); also elsewhere on the board
/PLL_SYNC: U14.6 (SYNC); also elsewhere on the board
/Sample clock muxing/PLL_SAMPCLK_N: U14.50 (CLKOUT7_N); also elsewhere on the board
/Sample clock muxing/PLL_SAMPCLK_P: U14.51 (CLKOUT7_P); also elsewhere on the board
unnamed: C116.2, R14.1
unnamed: C121.2, R15.1
unnamed: C127.2, U14.11 (LDObyp1)
unnamed: C128.2, U14.12 (LDObyp2)

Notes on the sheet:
PLL CONFIGURATION Loop 1 1.6 mA charge pump gain 25 MHz phase det Loop 2 3.2 mA charge pump gain 2.5 GHz Fvco 50 MHz PFD C3/C4 = 0.01 nF R3/R4 = 0.2K
PLL clock out for debugging
Debug test point
PLL2 loop filter
PLL1 loop filter
